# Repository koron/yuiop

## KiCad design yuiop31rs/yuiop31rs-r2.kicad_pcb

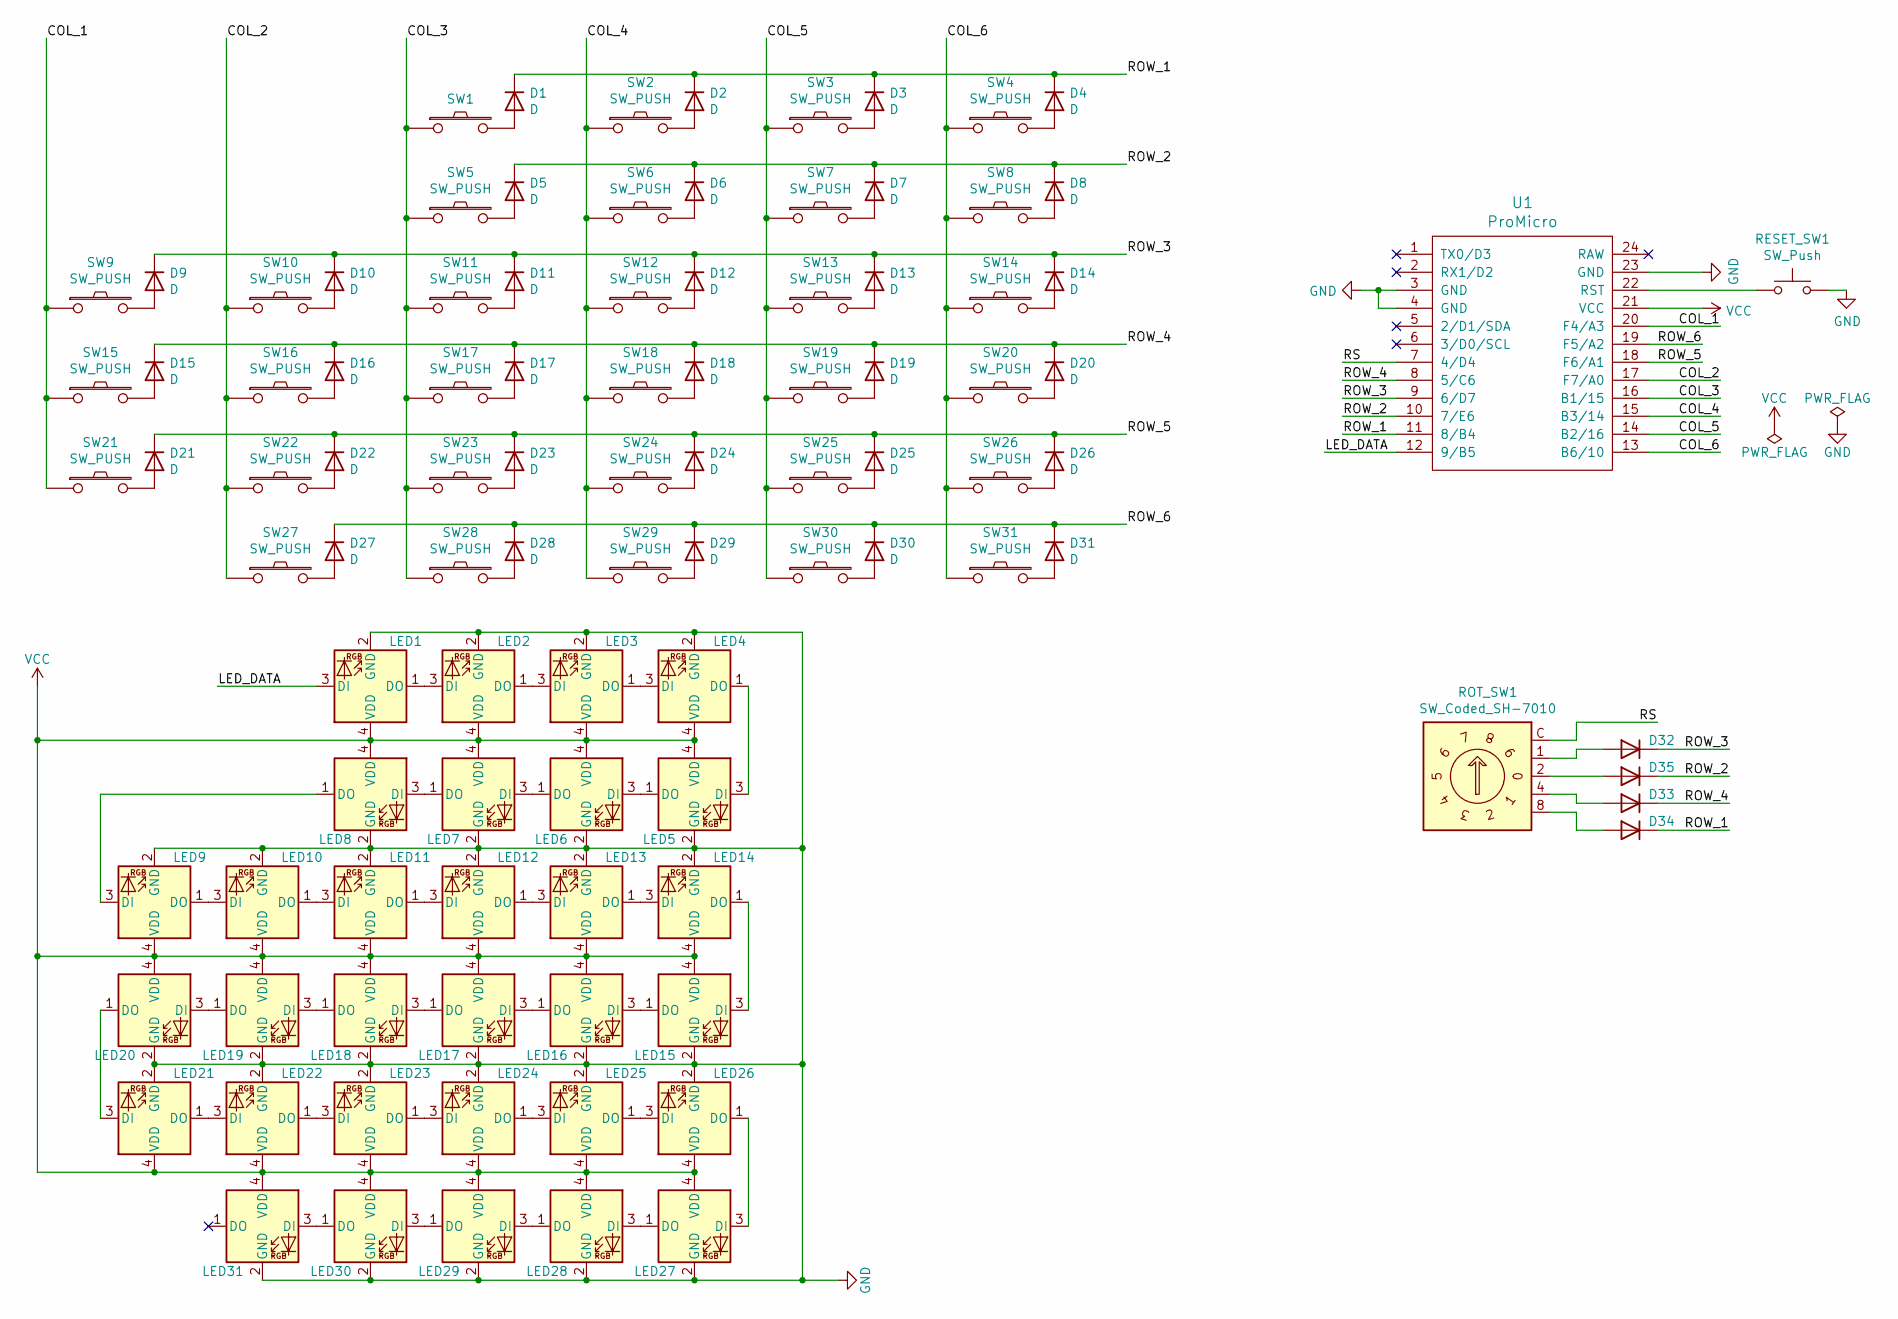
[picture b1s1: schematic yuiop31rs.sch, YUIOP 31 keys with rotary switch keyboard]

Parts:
D1, D2, D3, D4, D5, D6, D7, D8, D9, D10, D11, D12, D13, D14, D15, D16, D17, D18, D19, D20, D21, D22, D23, D24, D25, D26, D27, D28, D29, D30, D31, D32, D33, D34, D35: D; D_SOD-123
LED1, LED2, LED3, LED4, LED5, LED6, LED7, LED8, LED9, LED10, LED11, LED12, LED13, LED14, LED15, LED16, LED17, LED18, LED19, LED20, LED21, LED22, LED23, LED24, LED25, LED26, LED27, LED28, LED29, LED30, LED31: WS2812C-2020; LED_WS2812C-2020_BackMount
RESET_SW1: SW_Push; ResetSW_2_1side
ROT_SW1: SW_Coded_SH-7010; Nidec_Copal_SH-7010C
SW1, SW2, SW3, SW4, SW5, SW6, SW7, SW8, SW9, SW10, SW11, SW12, SW13, SW14, SW15, SW16, SW17, SW18, SW19, SW20, SW21, SW22, SW23, SW24, SW25, SW26, SW27, SW28, SW29, SW30, SW31: SW_PUSH; Cherry_MX_Hotswap_1.0u
U1: ProMicro; ProMicro_v3

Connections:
/COL_1: SW9.1, SW15.1, SW21.1, U1.20 (F4/A3)
/COL_2: SW10.1, SW16.1, SW22.1, SW27.1, U1.17 (F7/A0)
/COL_3: SW1.1, SW5.1, SW11.1, SW17.1, SW23.1, SW28.1, U1.16 (B1/15)
/COL_4: SW2.1, SW6.1, SW12.1, SW18.1, SW24.1, SW29.1, U1.15 (B3/14)
/COL_5: SW3.1, SW7.1, SW13.1, SW19.1, SW25.1, SW30.1, U1.14 (B2/16)
/COL_6: SW4.1, SW8.1, SW14.1, SW20.1, SW26.1, SW31.1, U1.13 (B6/10)
/LED_DATA: LED1.3 (DI), U1.12 (9/B5)
/ROW_1: D1.1 (K), D2.1 (K), D3.1 (K), D4.1 (K), D34.1 (K), U1.11 (8/B4)
/ROW_2: D5.1 (K), D6.1 (K), D7.1 (K), D8.1 (K), D35.1 (K), U1.10 (7/E6)
/ROW_3: D9.1 (K), D10.1 (K), D11.1 (K), D12.1 (K), D13.1 (K), D14.1 (K), D32.1 (K), U1.9 (6/D7)
/ROW_4: D15.1 (K), D16.1 (K), D17.1 (K), D18.1 (K), D19.1 (K), D20.1 (K), D33.1 (K), U1.8 (5/C6)
/ROW_5: D21.1 (K), D22.1 (K), D23.1 (K), D24.1 (K), D25.1 (K), D26.1 (K), U1.18 (F6/A1)
/ROW_6: D27.1 (K), D28.1 (K), D29.1 (K), D30.1 (K), D31.1 (K), U1.19 (F5/A2)
/RS: ROT_SW1.C, U1.7 (4/D4)
GND: LED1.2 (GND), LED2.2 (GND), LED3.2 (GND), LED4.2 (GND), LED5.2 (GND), LED6.2 (GND), LED7.2 (GND), LED8.2 (GND), LED9.2 (GND), LED10.2 (GND), LED11.2 (GND), LED12.2 (GND), LED13.2 (GND), LED14.2 (GND), LED15.2 (GND), LED16.2 (GND), LED17.2 (GND), LED18.2 (GND), LED19.2 (GND), LED20.2 (GND), LED21.2 (GND), LED22.2 (GND), LED23.2 (GND), LED24.2 (GND), LED25.2 (GND), LED26.2 (GND), LED27.2 (GND), LED28.2 (GND), LED29.2 (GND), LED30.2 (GND), LED31.2 (GND), RESET_SW1.2, U1.3 (GND), U1.4 (GND), U1.23 (GND)
unnamed: D1.2 (A), SW1.2
unnamed: D2.2 (A), SW2.2
unnamed: D3.2 (A), SW3.2
unnamed: D4.2 (A), SW4.2
unnamed: D5.2 (A), SW5.2
unnamed: D6.2 (A), SW6.2
unnamed: D7.2 (A), SW7.2
unnamed: D8.2 (A), SW8.2
unnamed: D9.2 (A), SW9.2
unnamed: D10.2 (A), SW10.2
unnamed: D11.2 (A), SW11.2
unnamed: D12.2 (A), SW12.2
unnamed: D13.2 (A), SW13.2
unnamed: D14.2 (A), SW14.2
unnamed: D15.2 (A), SW15.2
unnamed: D16.2 (A), SW16.2
unnamed: D17.2 (A), SW17.2
unnamed: D18.2 (A), SW18.2
unnamed: D19.2 (A), SW19.2
unnamed: D20.2 (A), SW20.2
unnamed: D21.2 (A), SW21.2
unnamed: D22.2 (A), SW22.2
unnamed: D23.2 (A), SW23.2
unnamed: D24.2 (A), SW24.2
unnamed: D25.2 (A), SW25.2
unnamed: D26.2 (A), SW26.2
unnamed: D27.2 (A), SW27.2
unnamed: D28.2 (A), SW28.2
unnamed: D29.2 (A), SW29.2
unnamed: D30.2 (A), SW30.2
unnamed: D31.2 (A), SW31.2
unnamed: D32.2 (A), ROT_SW1.1
unnamed: D33.2 (A), ROT_SW1.4
unnamed: D34.2 (A), ROT_SW1.8
unnamed: D35.2 (A), ROT_SW1.2
unnamed: LED1.1 (DO), LED2.3 (DI)
unnamed: LED2.1 (DO), LED3.3 (DI)
unnamed: LED3.1 (DO), LED4.3 (DI)
unnamed: LED4.1 (DO), LED5.3 (DI)
unnamed: LED5.1 (DO), LED6.3 (DI)
unnamed: LED6.1 (DO), LED7.3 (DI)
unnamed: LED7.1 (DO), LED8.3 (DI)
unnamed: LED8.1 (DO), LED9.3 (DI)
unnamed: LED10.1 (DO), LED11.3 (DI)
unnamed: LED9.1 (DO), LED10.3 (DI)
unnamed: LED11.1 (DO), LED12.3 (DI)
unnamed: LED12.1 (DO), LED13.3 (DI)
unnamed: LED13.1 (DO), LED14.3 (DI)
unnamed: LED14.1 (DO), LED15.3 (DI)
unnamed: LED15.1 (DO), LED16.3 (DI)
unnamed: LED16.1 (DO), LED17.3 (DI)
unnamed: LED17.1 (DO), LED18.3 (DI)
unnamed: LED18.1 (DO), LED19.3 (DI)
unnamed: LED19.1 (DO), LED20.3 (DI)
unnamed: LED20.1 (DO), LED21.3 (DI)
unnamed: LED21.1 (DO), LED22.3 (DI)
unnamed: LED22.1 (DO), LED23.3 (DI)
unnamed: LED23.1 (DO), LED24.3 (DI)
unnamed: LED24.1 (DO), LED25.3 (DI)
unnamed: LED25.1 (DO), LED26.3 (DI)
unnamed: LED26.1 (DO), LED27.3 (DI)
unnamed: LED27.1 (DO), LED28.3 (DI)
unnamed: LED28.1 (DO), LED29.3 (DI)
unnamed: LED29.1 (DO), LED30.3 (DI)
unnamed: LED30.1 (DO), LED31.3 (DI)
unnamed: RESET_SW1.1, U1.22 (RST)
VCC: LED1.4 (VDD), LED2.4 (VDD), LED3.4 (VDD), LED4.4 (VDD), LED5.4 (VDD), LED6.4 (VDD), LED7.4 (VDD), LED8.4 (VDD), LED9.4 (VDD), LED10.4 (VDD), LED11.4 (VDD), LED12.4 (VDD), LED13.4 (VDD), LED14.4 (VDD), LED15.4 (VDD), LED16.4 (VDD), LED17.4 (VDD), LED18.4 (VDD), LED19.4 (VDD), LED20.4 (VDD), LED21.4 (VDD), LED22.4 (VDD), LED23.4 (VDD), LED24.4 (VDD), LED25.4 (VDD), LED26.4 (VDD), LED27.4 (VDD), LED28.4 (VDD), LED29.4 (VDD), LED30.4 (VDD), LED31.4 (VDD), U1.21 (VCC)

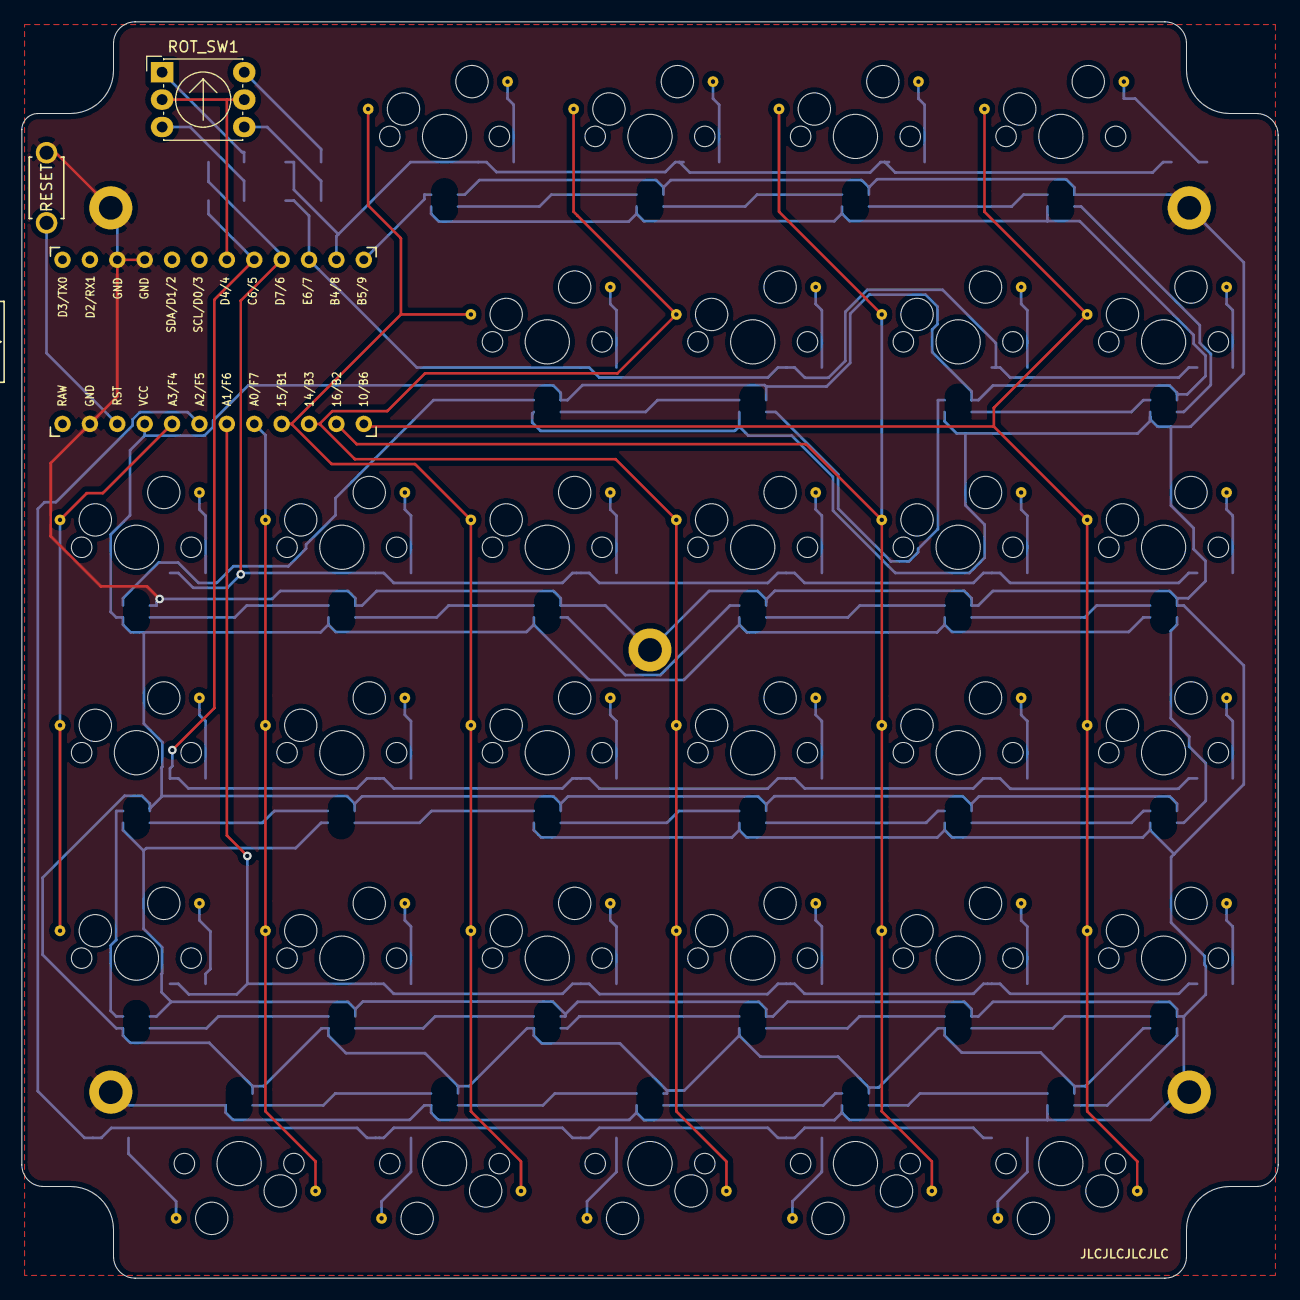
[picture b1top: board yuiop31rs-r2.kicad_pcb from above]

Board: 2 copper layers, 116.5 x 116.5 mm, 105 parts (0 on the bottom side), 82 nets.

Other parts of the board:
HOLE1, HOLE2, HOLE3, HOLE4, HOLE5: Hole_2.2_4
